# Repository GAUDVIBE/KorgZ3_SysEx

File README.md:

# Korg Z3 SysEx Controller

An Arduino Mega 2560-based MIDI controller for the **Korg Z3 FM synthesizer**, allowing real-time editing of all internal FM parameters via 16 analog potentiometers, organized across 5 pages.

> The Korg Z3 only accepts complete SysEx parameter dumps — this controller handles that constraint transparently, sending a full 96-byte dump on every parameter change.

---

## Features

- **16 potentiometers × 5 pages** = up to 80 parameters mapped to the Z3's FM engine
- **Live Dump Request** — fetch the current preset directly from the Z3 over MIDI
- **Up to 8 preset slots** stored in RAM, persisted to EEPROM (survives power-off)
- **Factory preset** (SynLead) loaded on first boot
- **Pickup mode** — pots are inactive until moved, preventing value jumps on page change
- **Adaptive filtering** — exponential smoothing + proportional deadband, tuned per parameter range
- **128×32 OLED display** — shows preset name, slot index, page, and live parameter values with auto-scroll
- **4 LEDs** with distinct behaviors for navigation, dump request, and memory operations

---

## Hardware

| Component | Detail |
|---|---|
| Microcontroller | Arduino Mega 2560 |
| Potentiometers | 16× analog, pins A0–A15 |
| Button − (page prev) | Digital pin 7 |
| Button + (page next) | Digital pin 8 |
| Button cycle/save | Digital pin 5 |
| Button Dump Request | Digital pin 6 |
| LED page − | Digital pin 12 |
| LED page + | Digital pin 11 |
| LED Dump Request | Digital pin 10 |
| LED slot | Digital pin 9 |
| OLED display | 128×32 I2C, SDA=20, SCL=21, address 0x3C |

> **Tip:** Adding a 100nF ceramic capacitor between each pot's wiper and GND significantly reduces ADC noise and improves parameter stability.

### PCB / KiCad design

A full KiCad reconstruction of the board (schematic + PCB) lives in [`hardware/`](hardware/),
rebuilt from the original Gerbers. It also includes an extension: a **CD74HC4067** analog
multiplexer (extra analog inputs + spare channels) and **RC anti-noise filters** (1 kΩ + 100 nF)
on every analog input. See
[`hardware/RECONSTRUCTION_SCHEMA.md`](hardware/RECONSTRUCTION_SCHEMA.md) and
[`hardware/ATTRIBUTION.md`](hardware/ATTRIBUTION.md) (hardware is CC BY-NC-SA, derived from
baritonomarchetto's design).

### Pitch wheel & bend range (v1.1)

A **pitch wheel** and a **3-position bend-range switch** are mounted **on the guitar** and connected
to the shield by a single 4-conductor cable through a **mini-XLR** socket. The switch selects the
musical amplitude of the wheel:

| Switch position | Bend range |
|---|---|
| 1 | ±1 tone |
| 2 | ±1.5 tones |
| 3 | ±1 octave |

The Korg Z3 hard-maps the full MIDI pitch-bend range `[0..16383]` onto ±12 semitones and offers no
way to change it. To obtain a smaller, more playable amplitude, the firmware restricts the range it
emits to `8192 ± N × 8192 / 12`.

Both inputs are read through the multiplexer: the wheel on channel 1, the switch on channel 2. The
switch is encoded as an analog voltage by a resistor ladder inside the guitar, which is what keeps
the cable down to four conductors.

**Unplugged-cable safety.** The three switch positions sit at ¼, ½ and ¾ of Vcc — never at 0 V. A
470 kΩ pull-down on the board means an unplugged cable reads ~0 V, a value belonging to no valid
position. The firmware therefore knows nothing is connected, freezes the pitch at centre and ignores
the wheel, instead of reading a floating input and emitting phantom pitch bend. The same channel thus
acts as both range selector and cable-presence detector.

Plugging the cable in also triggers an automatic calibration of the wheel's rest position, so the
controller no longer has to be powered on with the wheel centred.

---

## Button Behavior

| Button | Action |
|---|---|
| Pin 7 (−) | Previous page (I → V → IV → …) |
| Pin 8 (+) | Next page (I → II → … → V → I) |
| Pin 5 short press | Cycle through stored preset slots |
| Pin 5 long press ≥3s | Save current dump to memory (RAM + EEPROM) |
| Pin 6 long press ≥3s | Send Dump Request to Z3, receive and load the response |

## LED Behavior

| LED | Pin | Behavior |
|---|---|---|
| LED_PREV | 12 | Flashes 300ms on page − click |
| LED_NEXT | 11 | Flashes 300ms on page + click |
| LED_DUMP_REQ | 10 | Blinks continuously during Dump Request, off on receive/timeout |
| LED_SLOT | 9 | Solid = preset loaded from memory / Blinks 3× = save confirmed |

---

## Pages & Parameters

### Page I — Global & Levels
| Pot | Parameter | Range | SysEx offset |
|---|---|---|---|
| A0 | Algorithm | 0–7 | 13 |
| A5 | Feedback | 0–7 | 14 |
| A8 | LFO Wave | 0–3 | 15 |
| A12 | LFO Rate | 0–255 | 16 (hi) + 17 (lo) |
| A1 | PMD | 0–127 | 18 |
| A4 | PMS | 0–7 | 19 |
| A9 | AMD | 0–127 | 20 |
| A13 | AMS | 0–3 | 21 |
| A2 | M1 Wave | 0–7 | 22 |
| A6 | C1 Wave | 0–7 | 23 |
| A10 | M2 Wave | 0–7 | 24 |
| A14 | C2 Wave | 0–7 | 25 |
| A3 | M1 Level | 0–127 | 42 |
| A7 | C1 Level | 0–127 | 43 |
| A11 | M2 Level | 0–127 | 44 |
| A15 | C2 Level | 0–127 | 45 |

### Page II — Envelopes (Attack / Decay / Sustain / Decay2)
M1, C1, M2, C2 — Attack (0–31), Decay1 (0–31), Sustain (0–15), Decay2 (0–31) — offsets 46–61

### Page III — Release, EG Bias, Detune
M1, C1, M2, C2 — Release (0–15), EG Bias (0–3), Detune1 (0–7), Detune2 (0–3) — offsets 34–41, 62–65, 74–77

### Page IV — Multiply, AMS Enable, Key Scale
M1, C1, M2, C2 — Multiply1 (0–15), Multiply2 (0–15), AMS Enable (0–1), Key Scale (0–3) — offsets 26–33, 66–73

### Page V — Velocity, Keyboard Track, Reverb, Rate/op
M1, C1, M2, C2 — Velocity Int (0–15), Keyboard Track (0–15), Reverb (0–1), Rate (0–7) — offsets 78–93

---

## MIDI / SysEx Details

- **Baud rate:** 31250 (standard MIDI)
- **Dump Request:** `F0 42 30 1D 10 F7`
- **Dump header:** `F0 42 30 1D 40` + 8 bytes ASCII name + parameters + `F7`
- **Dump size:** 95–96 bytes
- **Send guard:** 300ms minimum between consecutive SysEx transmissions

### LFO Rate — 2-byte parameter
LFO Rate is the only 2-byte parameter in the Z3 dump:
- Offset 16 (hi-byte) = `val / 128` → `0x00` or `0x01`
- Offset 17 (lo-byte) = `val % 128` → `0x00`–`0x7F`

---

## EEPROM Layout

| Address | Content |
|---|---|
| 0 | Magic byte `0xA5` (initialized flag) |
| 1 | Preset count |
| 2 | Current slot index |
| 3 + n×108 | Slot n: 2B size + 10B name + 96B data |

**Total used:** 867 bytes out of 4096 available on the Mega.

---

## Filtering & Stability

The controller uses a multi-stage approach to eliminate ADC noise without sacrificing responsiveness:

1. **Exponential smoothing** — coefficient `7/8` for large ranges (≥31 values), `3/4` for small ranges
2. **Proportional deadband** — 10% of step width around each boundary, minimum 1 LSB
3. **Stability validation** — 8 consecutive identical readings required for ranges ≥127, 6 for smaller ranges
4. **Relative pickup** — on page/preset change, a pot must move ≥2 steps from its resting position before becoming active (prevents false triggers without requiring the pot to find an exact value)

---

## Libraries Required

Install via Arduino Library Manager:
- `Adafruit GFX Library`
- `Adafruit SSD1306`
- `Wire` (built-in)
- `EEPROM` (built-in)

---

## Project Background

Built around a custom board inspired by [baritonomarchetto's Arduino SysEx Patcher](https://www.instructables.com/MIDI-SysEx-Patcher-Ver2/). The Z3's FM engine requires complete parameter dumps for every edit — this controller manages that constraint internally, giving the user a seamless knob-per-function experience.

---

## License

MIT

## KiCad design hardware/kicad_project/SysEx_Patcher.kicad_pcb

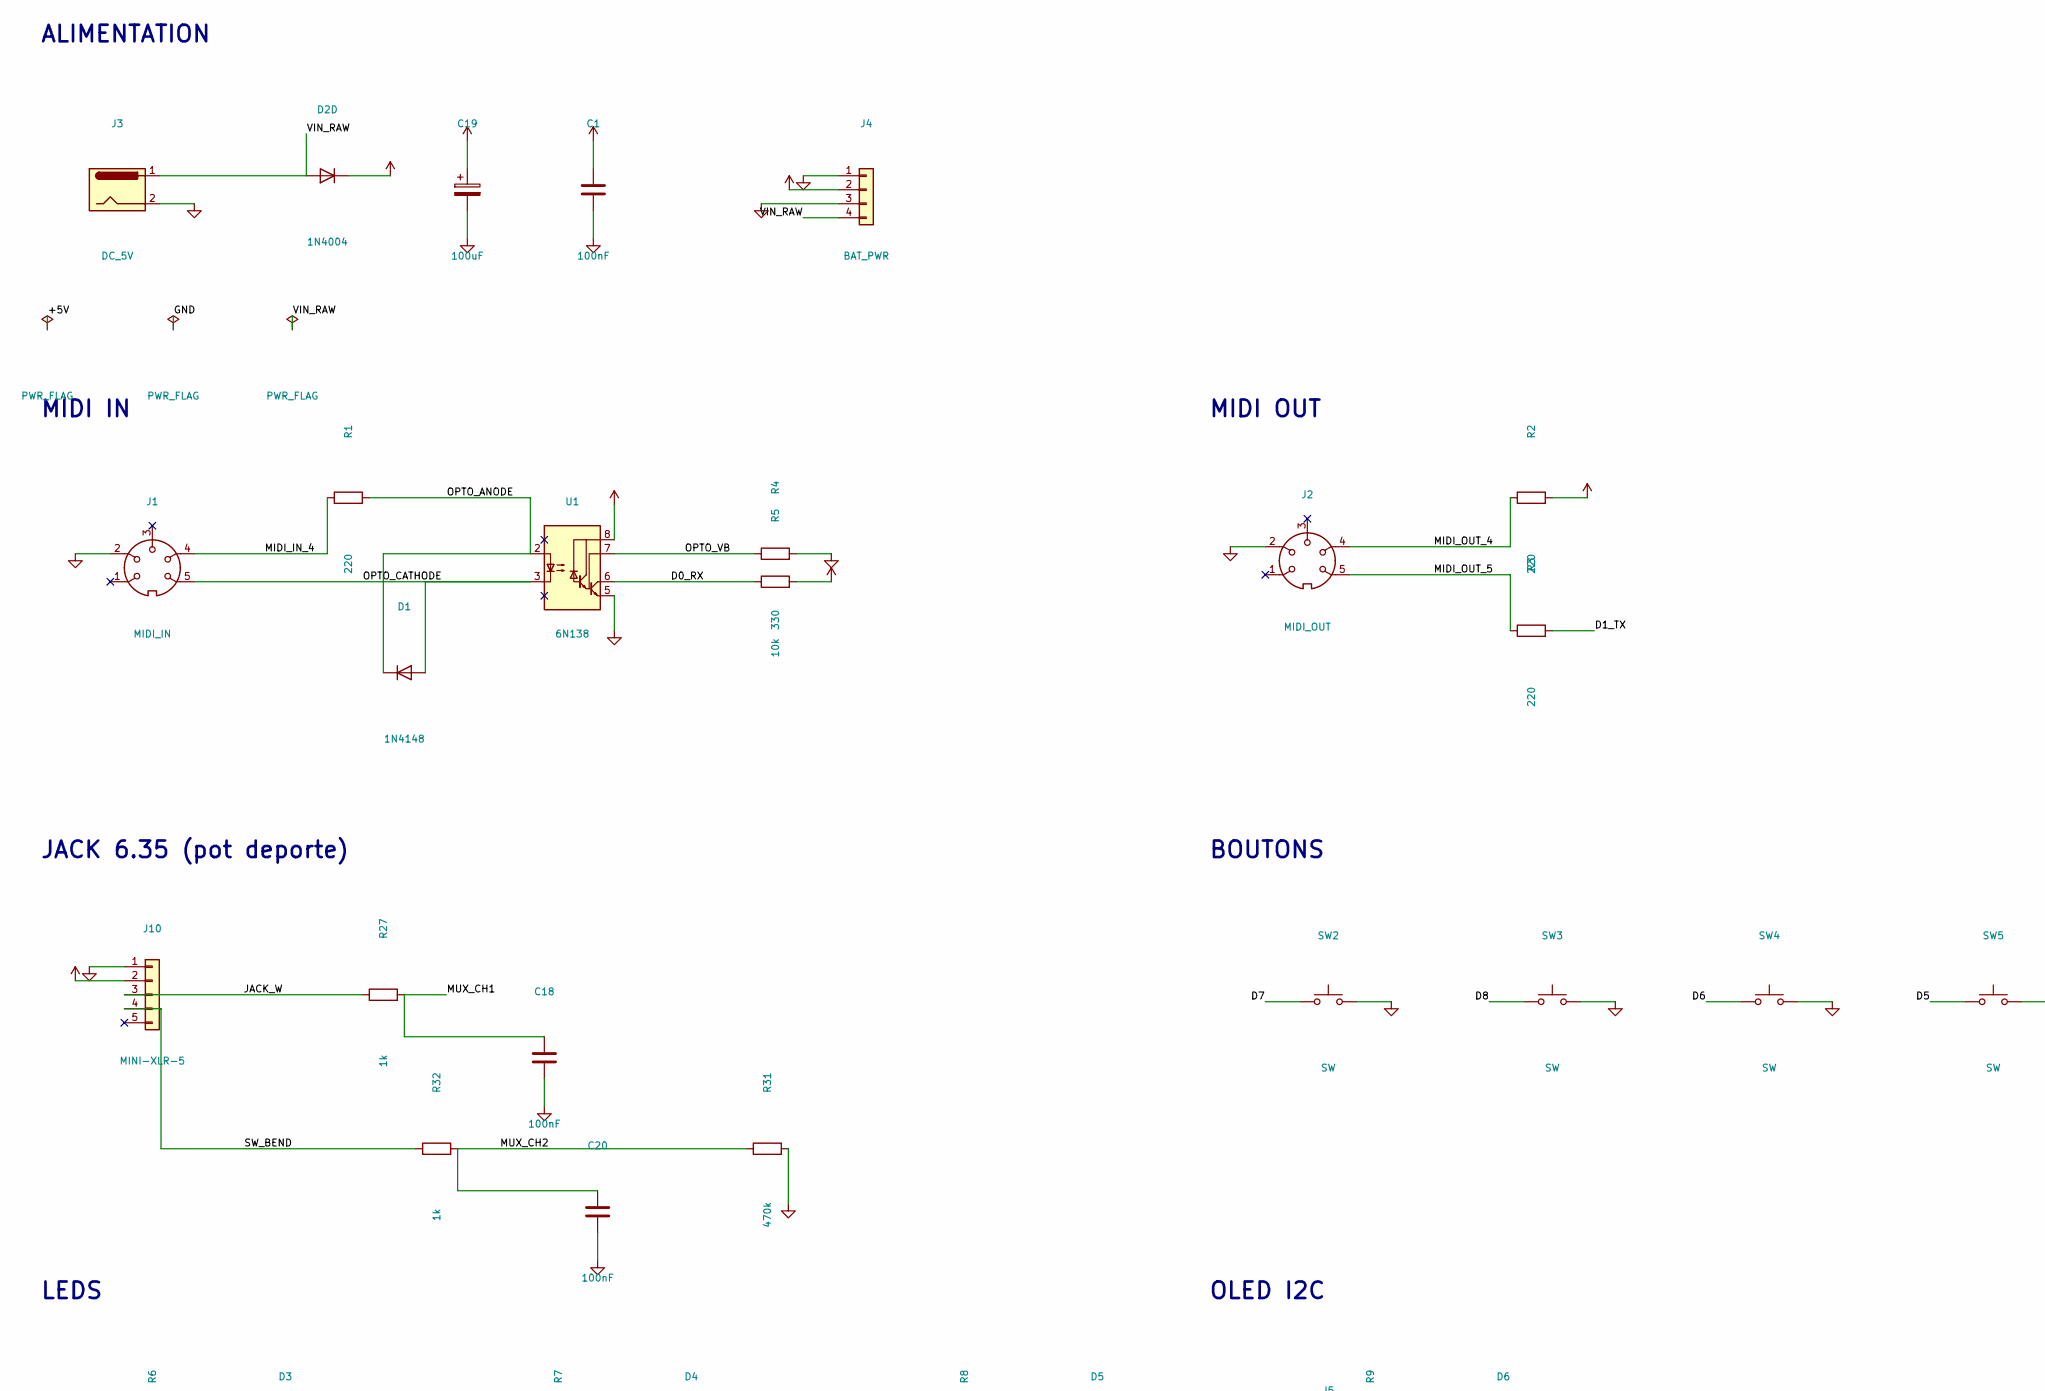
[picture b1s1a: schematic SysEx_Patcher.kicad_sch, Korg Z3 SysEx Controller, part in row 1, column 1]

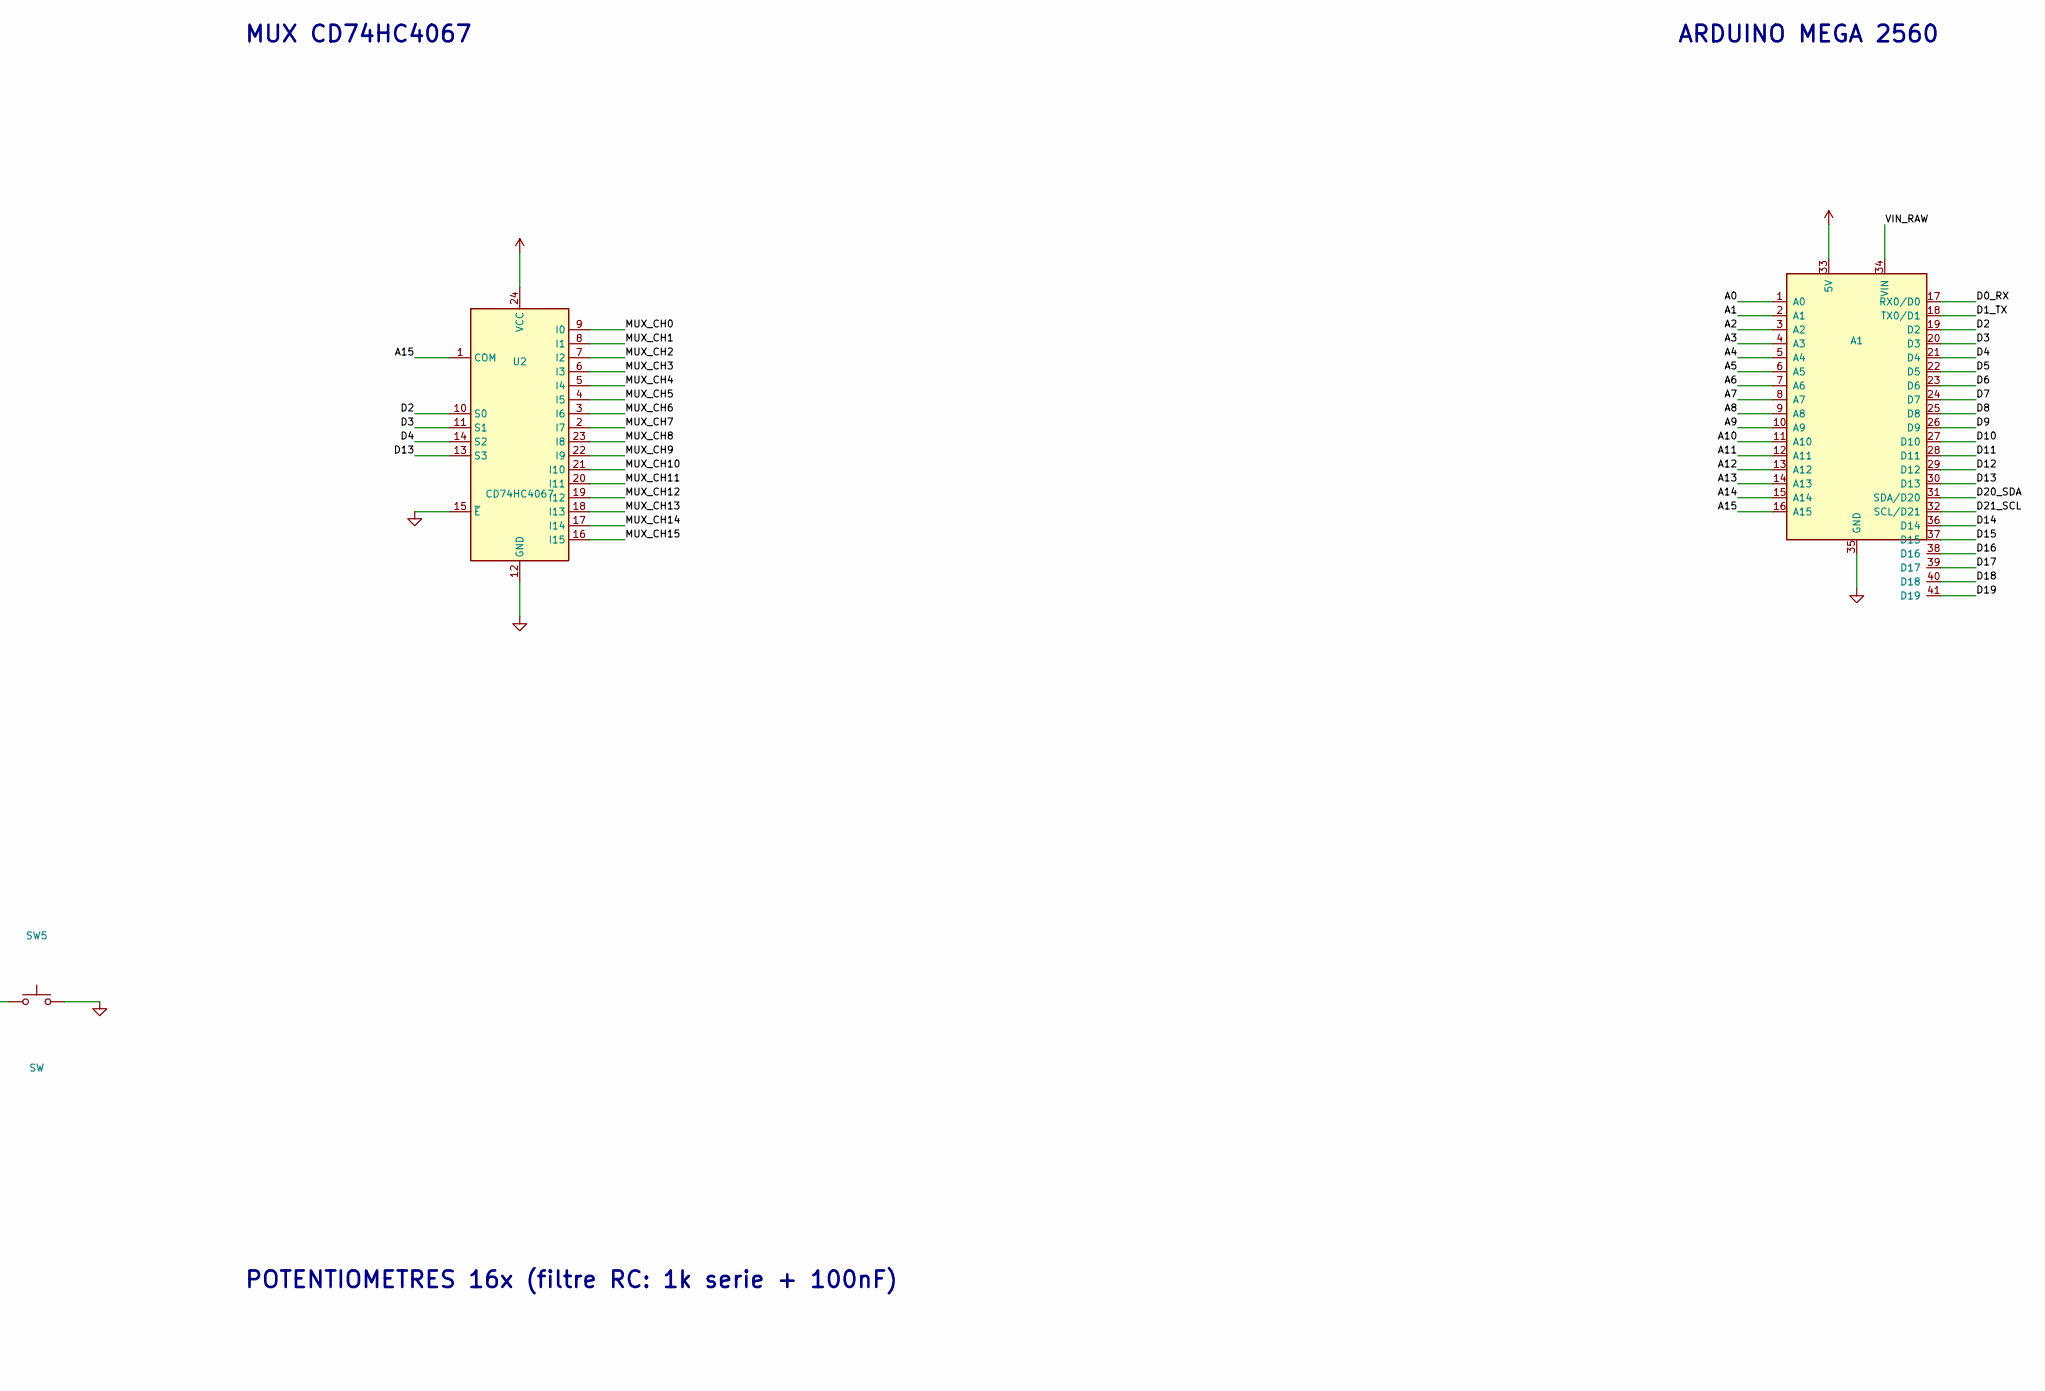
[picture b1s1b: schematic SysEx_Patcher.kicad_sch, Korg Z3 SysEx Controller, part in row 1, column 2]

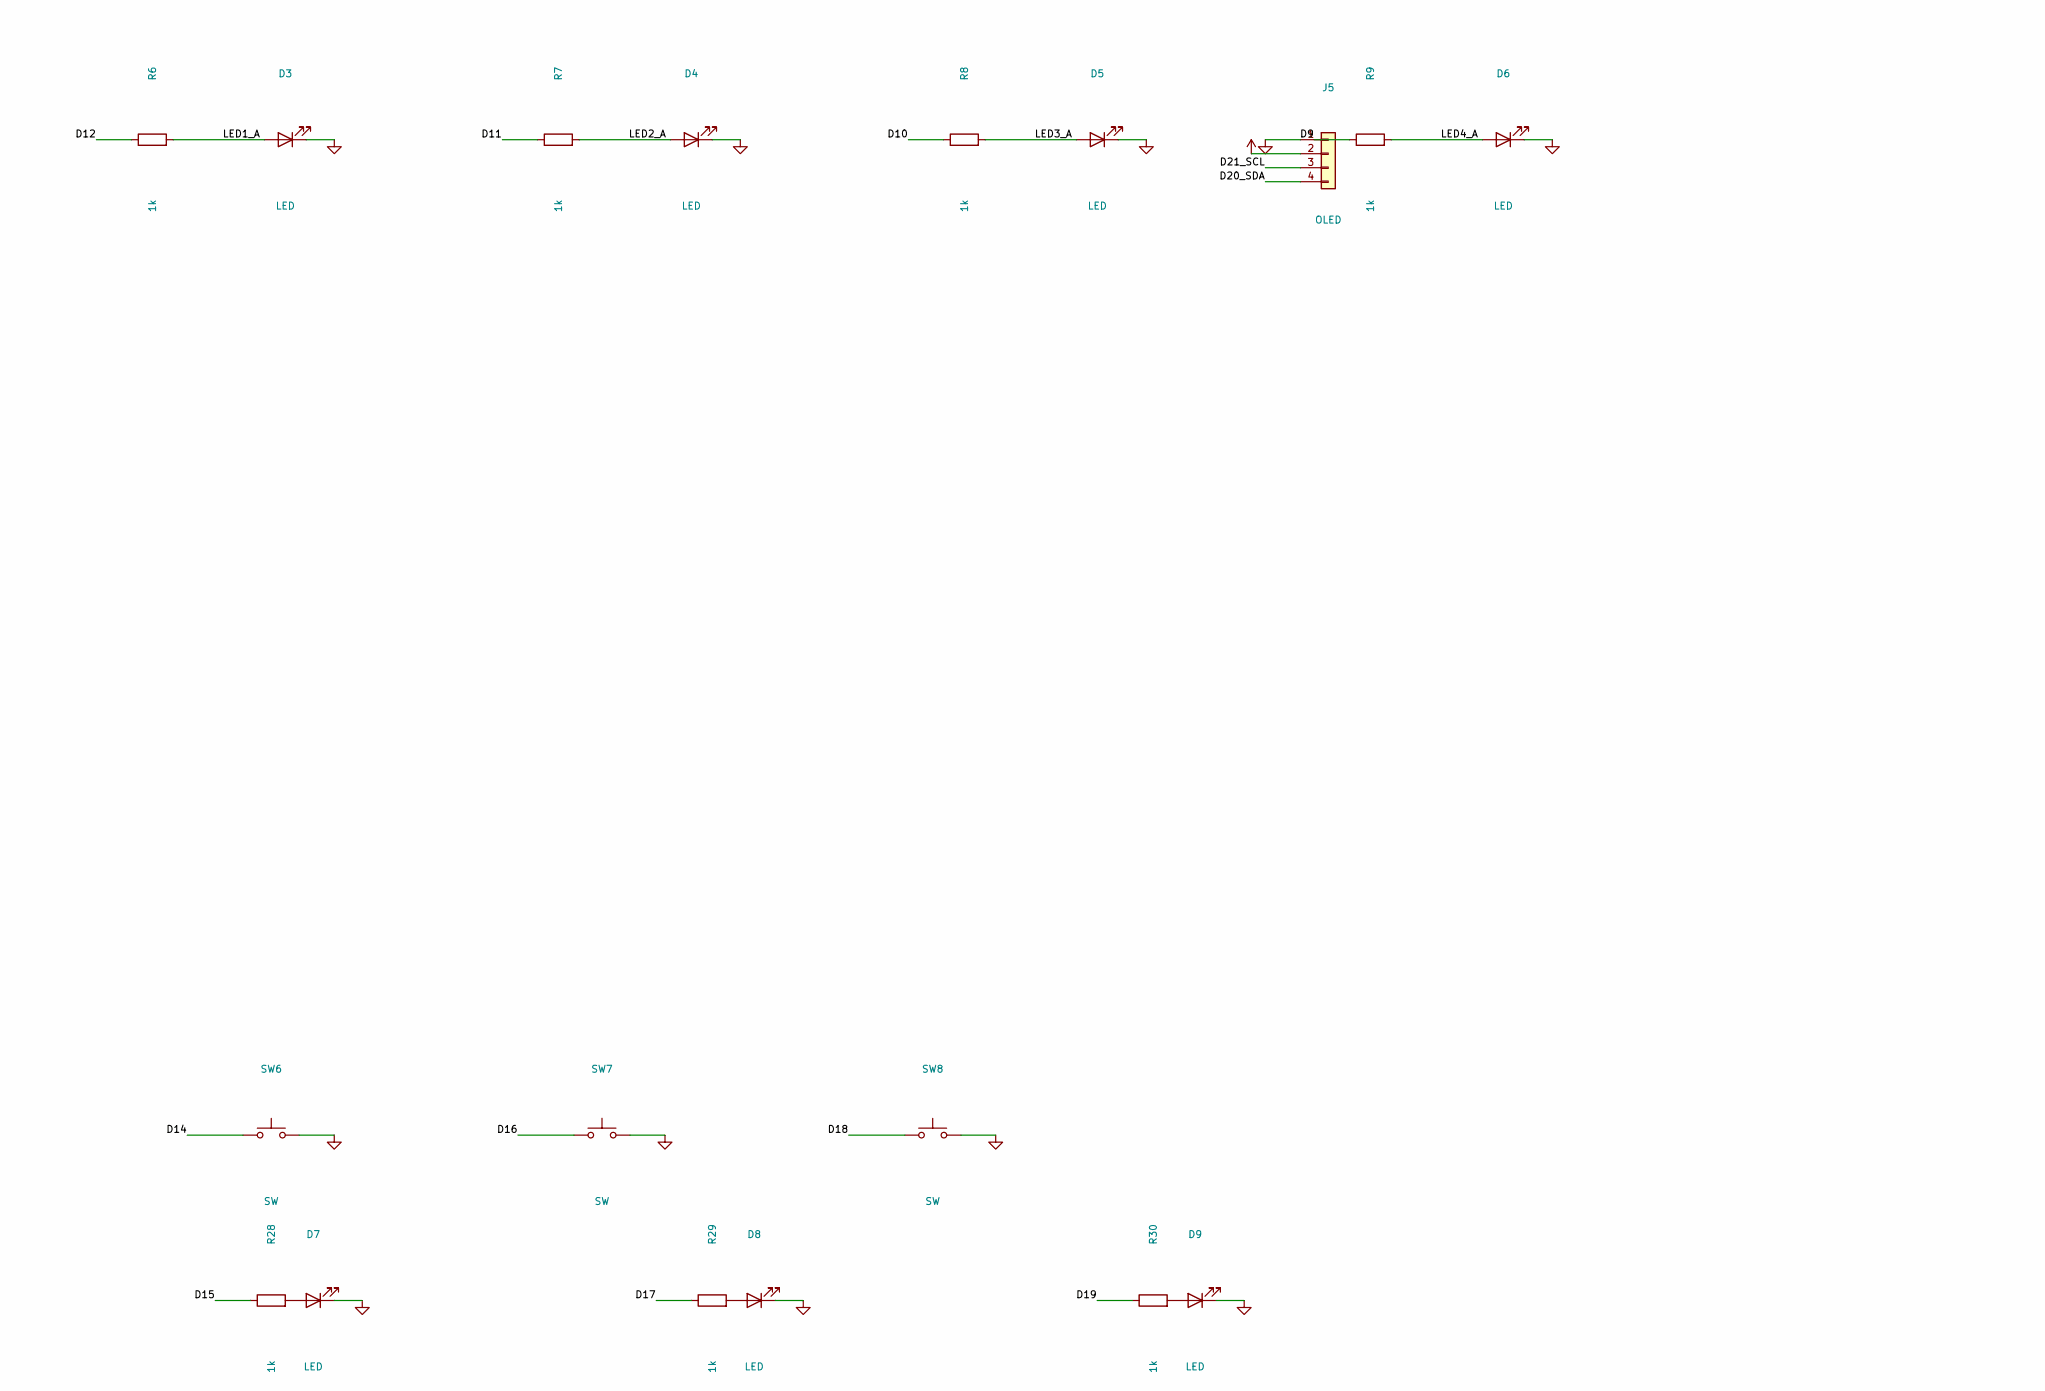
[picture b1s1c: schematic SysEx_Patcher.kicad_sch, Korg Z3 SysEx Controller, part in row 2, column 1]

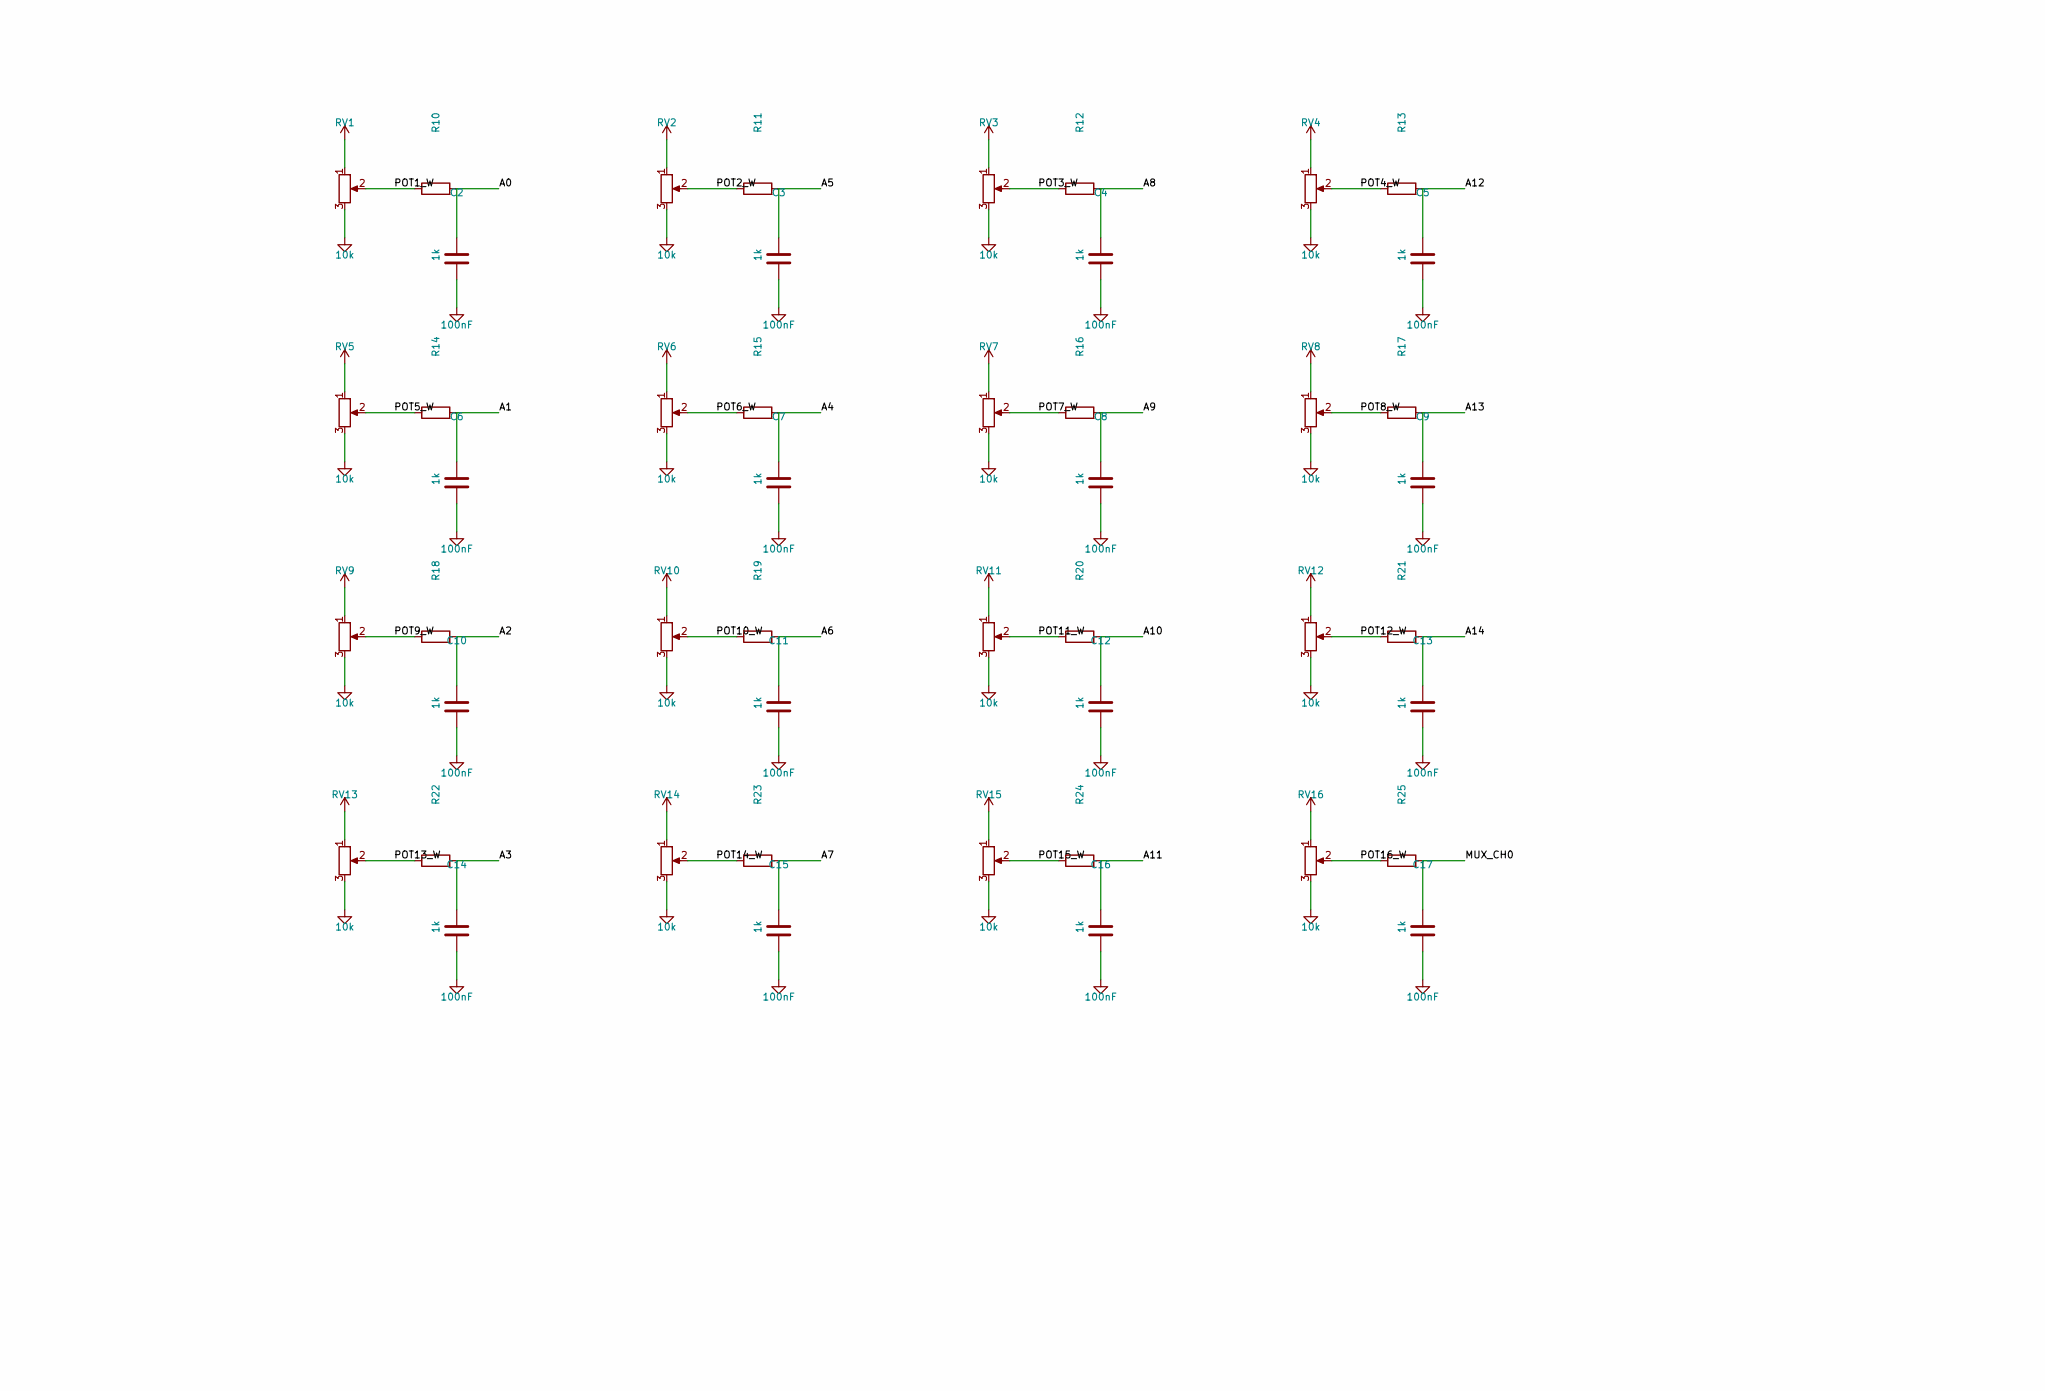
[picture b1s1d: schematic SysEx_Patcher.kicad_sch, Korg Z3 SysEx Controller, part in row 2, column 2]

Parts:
A1: Arduino_Mega2560
C1, C2, C3, C4, C5, C6, C7, C8, C9, C10, C11, C12, C13, C14, C15, C16, C17, C18, C20: 100nF; C_Disc_D5.0mm_W2.5mm_P5.00mm
C19: 100uF; CP_Radial_D6.3mm_P2.50mm
D1: 1N4148; D_DO-35_SOD27_P7.62mm_Horizontal
D2D: 1N4004; D_DO-41_SOD81_P10.16mm_Horizontal
D3, D4, D5, D6, D7, D8, D9: LED; LED_D3.0mm
J1: MIDI_IN; MIDI_DIN5_180deg
J2: MIDI_OUT; MIDI_DIN5_180deg
J3: DC_5V; BarrelJack_Horizontal
J4: BAT_PWR; PinHeader_1x04_P2.54mm_Vertical
J5: OLED; PinHeader_1x04_P2.54mm_Vertical
J10: MINI-XLR-5; MiniXLR-5_Switchcraft_TRAPC_Horizontal
R1, R2, R3: 220; R_Axial_DIN0207_L6.3mm_D2.5mm_P10.16mm_Horizontal
R4: 330; R_Axial_DIN0207_L6.3mm_D2.5mm_P10.16mm_Horizontal
R5: 10k; R_Axial_DIN0207_L6.3mm_D2.5mm_P10.16mm_Horizontal
R6, R7, R8, R9, R10, R11, R12, R13, R14, R15, R16, R17, R18, R19, R20, R21, R22, R23, R24, R25, R27, R28, R29, R30, R32: 1k; R_Axial_DIN0207_L6.3mm_D2.5mm_P10.16mm_Horizontal
R31: 470k; R_Axial_DIN0207_L6.3mm_D2.5mm_P10.16mm_Horizontal
RV1, RV2, RV3, RV4, RV5, RV6, RV7, RV8, RV9, RV10, RV11, RV12, RV13, RV14, RV15, RV16: 10k; Potentiometer_Alps_RK09K_Single_Vertical
SW2, SW3, SW4, SW5, SW6, SW7, SW8: SW; SW_PUSH_6mm
U1: 6N138; DIP-8_W7.62mm
U2: CD74HC4067; DIP-24_W15.24mm

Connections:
+5V: A1.33 (5V), C1.1, C19.1, D2D.1 (K), J4.2, J5.2, J10.2, R2.2, R5.2, RV1.1, RV2.1, RV3.1, RV4.1, RV5.1, RV6.1, RV7.1, RV8.1, RV9.1, RV10.1, RV11.1, RV12.1, RV13.1, RV14.1, RV15.1, RV16.1, U1.8 (VCC), U2.24 (VCC); also elsewhere on the board
A0: A1.1 (A0), C2.1, R10.2; also elsewhere on the board
A1: A1.2 (A1), C6.1, R14.2; also elsewhere on the board
A2: A1.3 (A2), C10.1, R18.2; also elsewhere on the board
A3: A1.4 (A3), C14.1, R22.2; also elsewhere on the board
A4: A1.5 (A4), C7.1, R15.2; also elsewhere on the board
A5: A1.6 (A5), C3.1, R11.2; also elsewhere on the board
A6: A1.7 (A6), C11.1, R19.2; also elsewhere on the board
A7: A1.8 (A7), C15.1, R23.2; also elsewhere on the board
A8: A1.9 (A8), C4.1, R12.2; also elsewhere on the board
A9: A1.10 (A9), C8.1, R16.2; also elsewhere on the board
A10: A1.11 (A10), C12.1, R20.2; also elsewhere on the board
A11: A1.12 (A11), C16.1, R24.2; also elsewhere on the board
A12: A1.13 (A12), C5.1, R13.2; also elsewhere on the board
A13: A1.14 (A13), C9.1, R17.2; also elsewhere on the board
A14: A1.15 (A14), C13.1, R21.2; also elsewhere on the board
A15: A1.16 (A15), U2.1 (COM); also elsewhere on the board
D0_RX: A1.17 (RX0/D0), R5.1, U1.6 (VO2); also elsewhere on the board
D1_TX: A1.18 (TX0/D1), R3.2; also elsewhere on the board
D2: A1.19 (D2), U2.10 (S0); also elsewhere on the board
D3: A1.20 (D3), U2.11 (S1); also elsewhere on the board
D4: A1.21 (D4), U2.14 (S2); also elsewhere on the board
D5: A1.22 (D5), SW5.1; also elsewhere on the board
D6: A1.23 (D6), SW4.1; also elsewhere on the board
D7: A1.24 (D7), SW2.1; also elsewhere on the board
D8: A1.25 (D8), SW3.1; also elsewhere on the board
D9: A1.26 (D9), R9.1; also elsewhere on the board
D10: A1.27 (D10), R8.1; also elsewhere on the board
D11: A1.28 (D11), R7.1; also elsewhere on the board
D12: A1.29 (D12), R6.1; also elsewhere on the board
D13: A1.30 (D13), U2.13 (S3); also elsewhere on the board
D14: A1.36 (D14), SW6.1; also elsewhere on the board
D15: A1.37 (D15), R28.1; also elsewhere on the board
D16: A1.38 (D16), SW7.1; also elsewhere on the board
D17: A1.39 (D17), R29.1; also elsewhere on the board
D18: A1.40 (D18), SW8.1; also elsewhere on the board
D19: A1.41 (D19), R30.1; also elsewhere on the board
D20_SDA: A1.31 (SDA/D20), J5.4; also elsewhere on the board
D21_SCL: A1.32 (SCL/D21), J5.3; also elsewhere on the board
GND: A1.35 (GND), C1.2, C2.2, C3.2, C4.2, C5.2, C6.2, C7.2, C8.2, C9.2, C10.2, C11.2, C12.2, C13.2, C14.2, C15.2, C16.2, C17.2, C18.2, C19.2, C20.2, D3.1 (K), D4.1 (K), D5.1 (K), D6.1 (K), D7.1 (K), D8.1 (K), D9.1 (K), J1.2, J2.2, J3.2, J4.1, J4.3, J5.1, J10.1, R4.2, R31.2, RV1.3, RV2.3, RV3.3, RV4.3, RV5.3, RV6.3, RV7.3, RV8.3, RV9.3, RV10.3, RV11.3, RV12.3, RV13.3, RV14.3, RV15.3, RV16.3, SW2.2, SW3.2, SW4.2, SW5.2, SW6.2, SW7.2, SW8.2, U1.5 (GND), U2.12 (GND), U2.15 (~E); also elsewhere on the board
JACK_W: J10.3, R27.1
LED1_A: D3.2 (A), R6.2
LED2_A: D4.2 (A), R7.2
LED3_A: D5.2 (A), R8.2
LED4_A: D6.2 (A), R9.2
LED5_A: D7.2 (A), R28.2
LED6_A: D8.2 (A), R29.2
LED7_A: D9.2 (A), R30.2
MIDI_IN_4: J1.4, R1.1
MIDI_OUT_4: J2.4, R2.1
MIDI_OUT_5: J2.5, R3.1
MUX_CH0: C17.1, R25.2, U2.9 (I0)
MUX_CH1: C18.1, R27.2, U2.8 (I1)
MUX_CH2: C20.1, R31.1, R32.2, U2.7 (I2)
MUX_CH3: U2.6 (I3)
MUX_CH4: U2.5 (I4)
MUX_CH5: U2.4 (I5)
MUX_CH6: U2.3 (I6)
MUX_CH7: U2.2 (I7)
MUX_CH8: U2.23 (I8)
MUX_CH9: U2.22 (I9)
MUX_CH10: U2.21 (I10)
MUX_CH11: U2.20 (I11)
MUX_CH12: U2.19 (I12)
MUX_CH13: U2.18 (I13)
MUX_CH14: U2.17 (I14)
MUX_CH15: U2.16 (I15)
OPTO_ANODE: D1.1 (K), R1.2, U1.2 (C1)
OPTO_CATHODE: D1.2 (A), J1.5, U1.3 (C2)
OPTO_VB: R4.1, U1.7 (VO1)
POT1_W: R10.1, RV1.2
POT2_W: R11.1, RV2.2
POT3_W: R12.1, RV3.2
POT4_W: R13.1, RV4.2
POT5_W: R14.1, RV5.2
POT6_W: R15.1, RV6.2
POT7_W: R16.1, RV7.2
POT8_W: R17.1, RV8.2
POT9_W: R18.1, RV9.2
POT10_W: R19.1, RV10.2
POT11_W: R20.1, RV11.2
POT12_W: R21.1, RV12.2
POT13_W: R22.1, RV13.2
POT14_W: R23.1, RV14.2
POT15_W: R24.1, RV15.2
POT16_W: R25.1, RV16.2
SW_BEND: J10.4, R32.1
VIN_RAW: A1.34 (VIN), D2D.2 (A), J3.1, J4.4; also elsewhere on the board

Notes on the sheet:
ALIMENTATION
MIDI IN
MIDI OUT
JACK 6.35 (pot deporte)
BOUTONS
LEDS
OLED I2C
MUX CD74HC4067
ARDUINO MEGA 2560
POTENTIOMETRES 16x (filtre RC: 1k serie + 100nF)

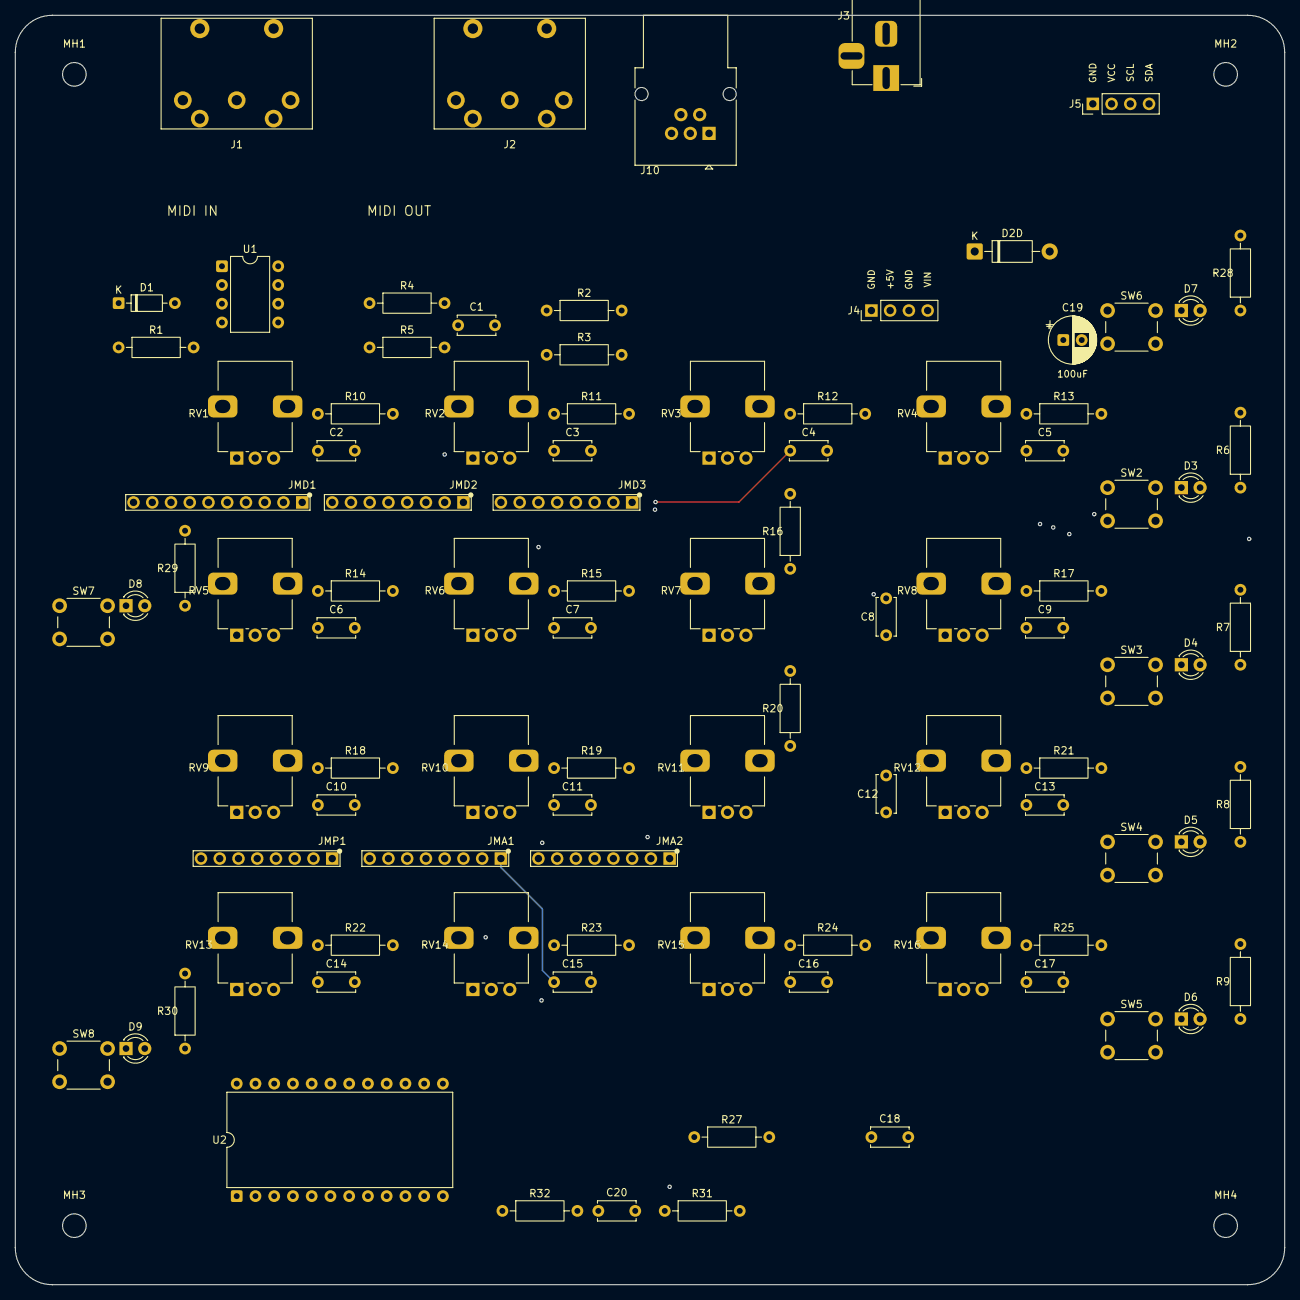
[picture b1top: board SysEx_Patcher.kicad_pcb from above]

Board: 4 copper layers, 172.0 x 172.0 mm, 101 parts (0 on the bottom side), 75 nets.

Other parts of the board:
JMA1, JMA2: MEGA_HDR; PinHeader_1x08_P2.54mm_Vertical
JMD1: MEGA_HDR; PinHeader_1x10_P2.54mm_Vertical
JMD2, JMD3: MEGA_HDR; PinHeader_1x08_P2.54mm_Vertical
JMP1: MEGA_HDR; PinHeader_1x08_P2.54mm_Vertical
MH1, MH2, MH3, MH4: MountingHole_3.2mm_M3

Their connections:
+5V: JMP1.4; also elsewhere on the board
A0: JMA1.8; also elsewhere on the board
A1: JMA1.7; also elsewhere on the board
A2: JMA1.6; also elsewhere on the board
A3: JMA1.5; also elsewhere on the board
A4: JMA1.4; also elsewhere on the board
A5: JMA1.3; also elsewhere on the board
A6: JMA1.2; also elsewhere on the board
A7: JMA1.1; also elsewhere on the board
A8: JMA2.8; also elsewhere on the board
A9: JMA2.7; also elsewhere on the board
A10: JMA2.6; also elsewhere on the board
A11: JMA2.5; also elsewhere on the board
A12: JMA2.4; also elsewhere on the board
A13: JMA2.3; also elsewhere on the board
A14: JMA2.2; also elsewhere on the board
A15: JMA2.1; also elsewhere on the board
D0_RX: JMD2.1; also elsewhere on the board
D1_TX: JMD2.2; also elsewhere on the board
D2: JMD2.3; also elsewhere on the board
D3: JMD2.4; also elsewhere on the board
D4: JMD2.5; also elsewhere on the board
D5: JMD2.6; also elsewhere on the board
D6: JMD2.7; also elsewhere on the board
D7: JMD2.8; also elsewhere on the board
D8: JMD1.1; also elsewhere on the board
D9: JMD1.2; also elsewhere on the board
D10: JMD1.3; also elsewhere on the board
D11: JMD1.4; also elsewhere on the board
D12: JMD1.5; also elsewhere on the board
D13: JMD1.6; also elsewhere on the board
D14: JMD3.8; also elsewhere on the board
D15: JMD3.7; also elsewhere on the board
D16: JMD3.6; also elsewhere on the board
D17: JMD3.5; also elsewhere on the board
D18: JMD3.4; also elsewhere on the board
D19: JMD3.3; also elsewhere on the board
D20_SDA: JMD1.9, JMD3.2; also elsewhere on the board
D21_SCL: JMD1.10, JMD3.1; also elsewhere on the board
GND: JMD1.7, JMP1.2, JMP1.3; also elsewhere on the board
VIN_RAW: JMP1.1; also elsewhere on the board
